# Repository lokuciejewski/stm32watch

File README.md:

# STM32 Watch

## Summary

This project is a simplistic STM32L031K6-based hand watch. It uses two HP's HPDL1414 displays to display up to 6 alphanumeric signs (though only capital letters). For timekeeping I decided to go with DS3231MZ+ and the whole thing is programmed in C using STM32CubeIDE.

## Main functions

New, HCMS-2904 version:

Apart from keeping the time and date, the watch is capable of adjusting its brightness automatically and displaying battery voltage. It uses USB type C for convenient charging (not compatible with chargers that require device ID to be sent) and includes a LED to indicate charging status.

Old, HPDL-1414 version:
Apart from keeping the time and date, the watch is capable of displaying the current ambient temperature and pressure, courtesy of Bosch BMP280 (which can be hot-swapped for BME280 for additional humidity data) and battery voltage. The watch is also equipped with two user-programmable LEDs - green and red by default, one charging indicator LED - yellow and a vibration motor (also fully programmable). It uses USB type C for convenient charging, though it is not compatible with some of the USB-C chargers (those that require device ID to be sent).

## PCB design

The design is currently WIP as the first prototype using HPDL-1414 was produced and verified. The new design will include HCMS-2904 as a replacement and will drop some features and gain some new ones, streamlining the design.

## Case design

There is a simple WIP case design for the HPDL-1414 version, more will come once the new HCMS-2904 pcb is finished.

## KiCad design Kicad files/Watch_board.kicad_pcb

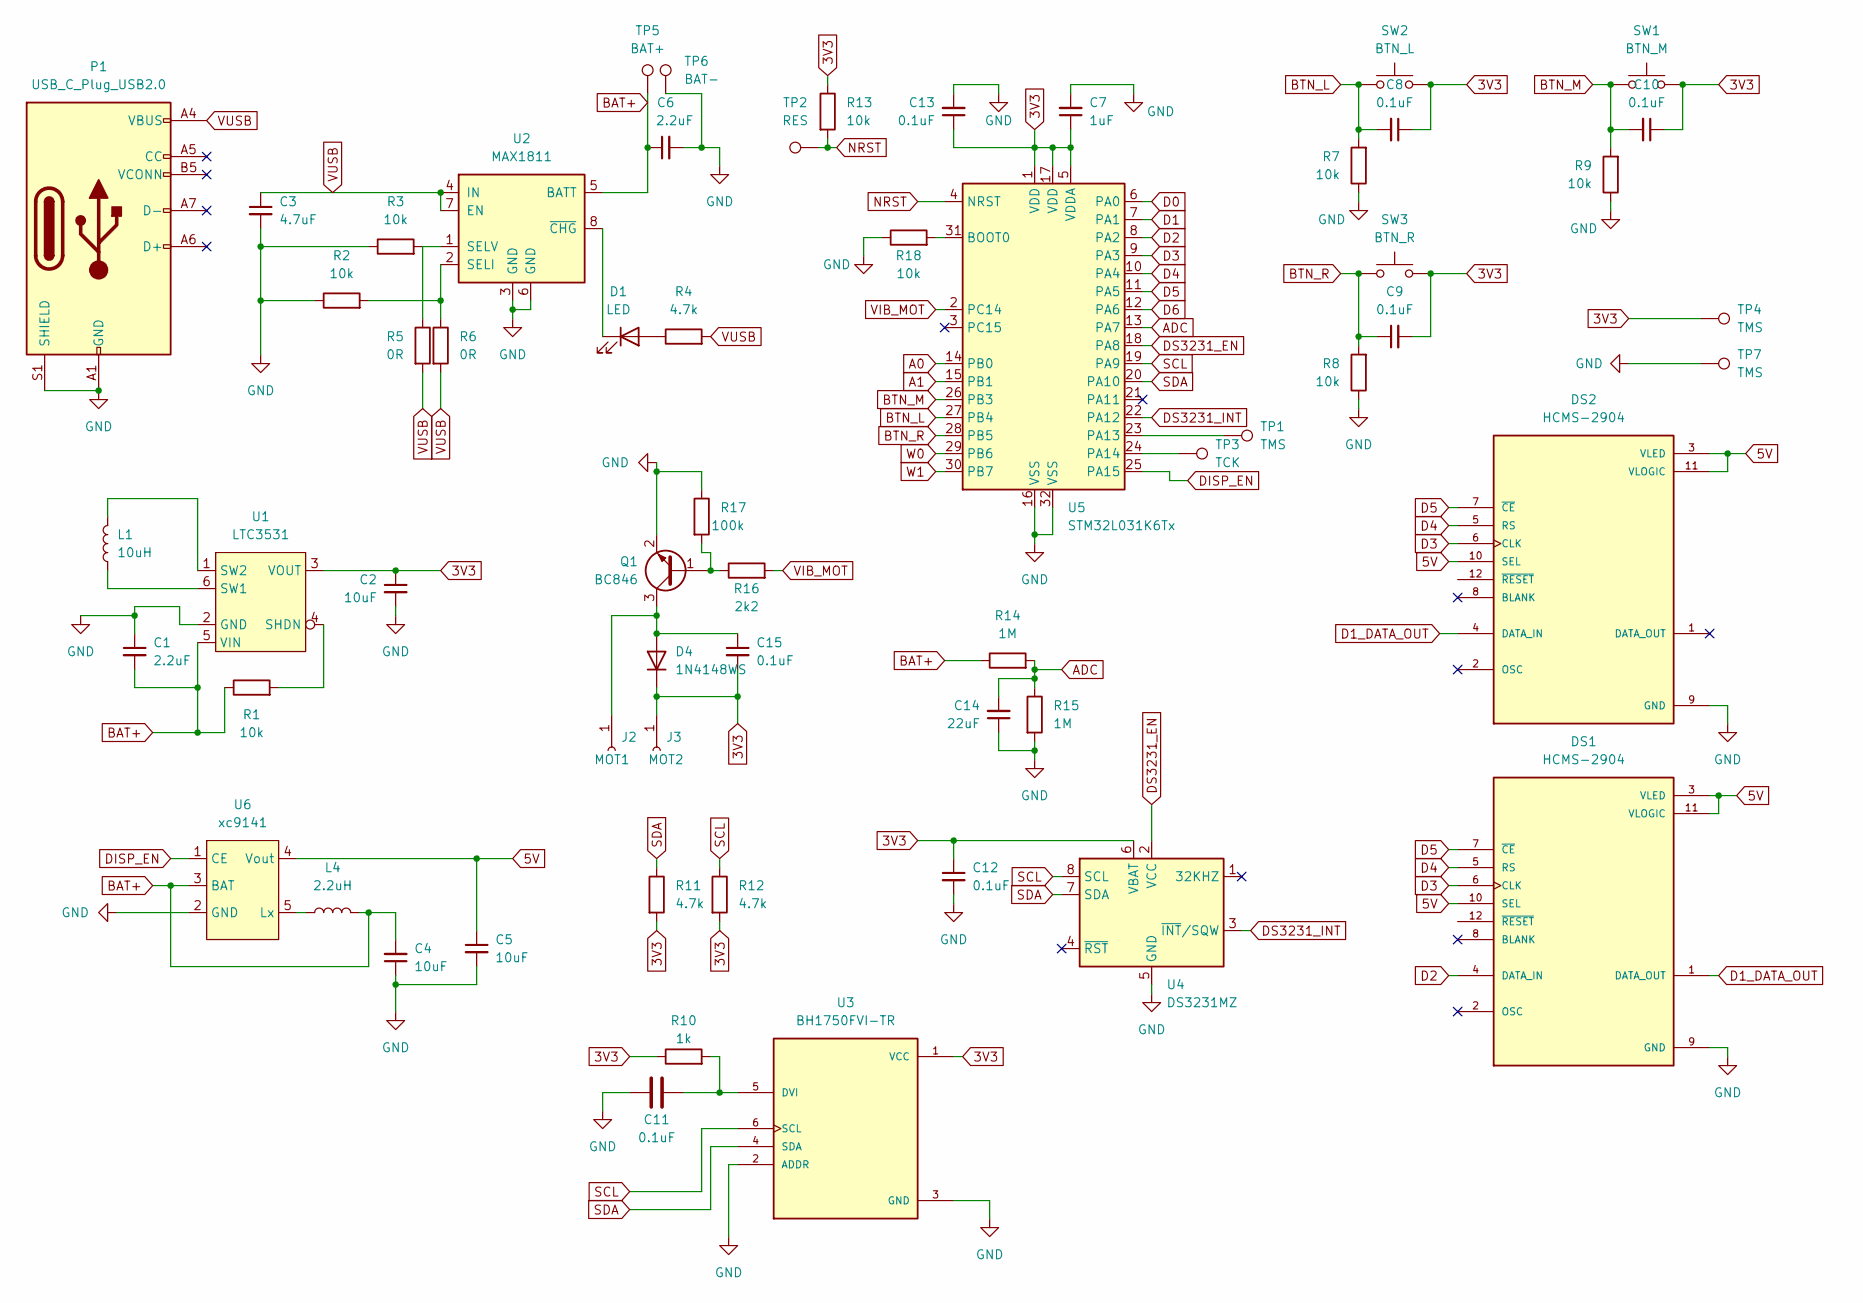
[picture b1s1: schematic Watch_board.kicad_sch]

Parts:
C1, C6: 2.2uF; C_0603_1608Metric_Pad1.08x0.95mm_HandSolder
C2, C4, C5: 10uF; C_0603_1608Metric_Pad1.08x0.95mm_HandSolder
C3: 4.7uF; C_0603_1608Metric_Pad1.08x0.95mm_HandSolder
C7: 1uF; C_0603_1608Metric_Pad1.08x0.95mm_HandSolder
C8, C9, C10, C11, C12, C13, C15: 0.1uF; C_0603_1608Metric_Pad1.08x0.95mm_HandSolder
C14: 22uF; C_0603_1608Metric_Pad1.08x0.95mm_HandSolder
D1: LED; LED_1206_3216Metric_Pad1.42x1.75mm_HandSolder
D4: 1N4148WS; D_SOD-323
DS1, DS2: HCMS-2904; DIPS762W51P254L1778H508Q12; PARTREV N/A
J2: MOT1; TestPoint_Pad_D2.0mm
J3: MOT2; TestPoint_Pad_D2.0mm
L1: 10uH; L_0603_1608Metric_Pad1.05x0.95mm_HandSolder
L4: 2.2uH; L_0603_1608Metric_Pad1.05x0.95mm_HandSolder
P1: USB_C_Plug_USB2.0; TYPE-C-31-M-17_handsolder
Q1: BC846; SOT-23
R1, R2, R3, R7, R8, R9, R13, R18: 10k; R_0603_1608Metric_Pad0.98x0.95mm_HandSolder
R4, R11, R12: 4.7k; R_0603_1608Metric_Pad0.98x0.95mm_HandSolder
R5, R6: 0R; R_0603_1608Metric_Pad0.98x0.95mm_HandSolder
R10: 1k; R_0603_1608Metric_Pad0.98x0.95mm_HandSolder
R14, R15: 1M; R_0603_1608Metric_Pad0.98x0.95mm_HandSolder
R16: 2k2; R_0603_1608Metric_Pad0.98x0.95mm_HandSolder
R17: 100k; R_0603_1608Metric_Pad0.98x0.95mm_HandSolder
SW1: BTN_M; SW_SPST_PTS810
SW2: BTN_L; SW_SPST_PTS810
SW3: BTN_R; SW_SPST_PTS810
TP1, TP4, TP7: TMS; TestPoint_Pad_1.5x1.5mm
TP2: RES; TestPoint_Pad_1.5x1.5mm
TP3: TCK; TestPoint_Pad_1.5x1.5mm
TP5: BAT+; TestPoint_Pad_1.5x1.5mm
TP6: BAT-; TestPoint_Pad_1.5x1.5mm
U1: LTC3531; TSOT-23-6
U2: MAX1811; SOIC-8_3.9x4.9mm_P1.27mm
U3: BH1750FVI-TR; XDCR_BH1750FVI-TR; PARTREV D
U4: DS3231MZ; SOIC-8_3.9x4.9mm_P1.27mm
U5: STM32L031K6Tx; LQFP-32_7x7mm_P0.8mm
U6: xc9141; SOT-23-5

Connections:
3V3: C2.1, C7.1, C8.1, C9.2, C10.1, C12.1, C13.1, C15.2, D4.1 (K), J3.1, R10.1, R11.2, R12.2, R13.1, SW1.2, SW2.2, SW3.2, TP4.1, U1.3 (VOUT), U3.1 (VCC), U4.6 (VBAT), U5.1 (VDD), U5.5 (VDDA), U5.17 (VDD)
5V: C5.1, DS1.3 (VLED), DS1.10 (SEL), DS1.11 (VLOGIC), DS2.3 (VLED), DS2.10 (SEL), DS2.11 (VLOGIC), U6.4 (Vout)
A0: U5.14 (PB0)
A1: U5.15 (PB1)
ADC: C14.2, R14.2, R15.1, U5.13 (PA7)
BAT+: C1.2, C4.2, C6.1, L4.2, R1.1, R14.1, TP5.1, U1.5 (VIN), U2.5 (BATT), U6.3 (BAT)
BTN_L: C8.2, R7.2, SW2.1, U5.27 (PB4)
BTN_M: C10.2, R9.2, SW1.1, U5.26 (PB3)
BTN_R: C9.1, R8.2, SW3.1, U5.28 (PB5)
D0: U5.6 (PA0)
D1: U5.7 (PA1)
D1_DATA_OUT: DS1.1 (DATA_OUT), DS2.4 (DATA_IN)
D2: DS1.4 (DATA_IN), U5.8 (PA2)
D3: DS1.6 (CLK), DS2.6 (CLK), U5.9 (PA3)
D4: DS1.5 (RS), DS2.5 (RS), U5.10 (PA4)
D5: DS1.7 (~CE), DS2.7 (~CE), U5.11 (PA5)
D6: U5.12 (PA6)
DISP_EN: U5.25 (PA15), U6.1 (CE)
DS3231_EN: U4.2 (VCC), U5.18 (PA8)
DS3231_INT: U4.3 (~INT/SQW), U5.22 (PA12)
GND: C1.1, C2.2, C3.2, C4.1, C5.2, C6.2, C7.2, C11.1, C12.2, C13.2, C14.1, DS1.9 (GND), DS2.9 (GND), P1.A1 (GND), P1.A12 (GND), P1.B1 (GND), P1.B12 (GND), P1.S1 (SHIELD), Q1.2 (E), R2.1, R3.1, R7.1, R8.1, R9.1, R15.2, R17.1, R18.1, TP6.1, TP7.1, U1.2 (GND), U2.3 (GND), U2.6 (GND), U3.2 (ADDR), U3.3 (GND), U4.5 (GND), U5.16 (VSS), U5.32 (VSS), U6.2 (GND)
NRST: R13.2, TP2.1, U5.4 (NRST)
unnamed: D1.2 (A), R4.1
unnamed: D1.1 (K), U2.8 (~CHG)
unnamed: C15.1, D4.2 (A), J2.1, Q1.3 (C)
unnamed: Q1.1 (B), R16.1, R17.2
unnamed: R1.2, U1.4 (SHDN)
unnamed: L1.1, U1.6 (SW1)
unnamed: L1.2, U1.1 (SW2)
unnamed: R2.2, R6.1, U2.2 (SELI)
unnamed: R3.2, R5.1, U2.1 (SELV)
unnamed: C11.2, R10.2, U3.5 (DVI)
unnamed: R18.2, U5.31 (BOOT0)
unnamed: TP1.1, U5.23 (PA13)
unnamed: TP3.1, U5.24 (PA14)
unnamed: L4.1, U6.5 (Lx)
SCL: R12.1, U3.6 (SCL), U4.8 (SCL), U5.19 (PA9)
SDA: R11.1, U3.4 (SDA), U4.7 (SDA), U5.20 (PA10)
VIB_MOT: R16.2, U5.2 (PC14)
VUSB: C3.1, P1.A4 (VBUS), P1.A9 (VBUS), P1.B4 (VBUS), P1.B9 (VBUS), R4.2, R5.2, R6.2, U2.4 (IN), U2.7 (EN)
W0: U5.29 (PB6)
W1: U5.30 (PB7)

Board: 2 copper layers, 58 parts (0 on the bottom side), 35 nets, no tracks yet.

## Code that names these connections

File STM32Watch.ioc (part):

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Mcu.Name=STM32L031K(4-6)Tx
Mcu.Package=LQFP32
Mcu.UserName=STM32L031K6Tx
PA0-CK_IN.GPIOParameters=GPIO_PuPd,GPIO_Label
PA0-CK_IN.GPIO_Label=D0
PA0-CK_IN.GPIO_PuPd=GPIO_NOPULL
PA0-CK_IN.Signal=GPIO_Output
PA1.GPIOParameters=GPIO_PuPd,GPIO_Label
PA1.GPIO_Label=D1
PA1.GPIO_PuPd=GPIO_NOPULL
PA1.Signal=GPIO_Output
PA10.Mode=I2C
PA10.Signal=I2C1_SDA
PA11.GPIOParameters=GPIO_Label
PA11.GPIO_Label=LED_R
PA11.Signal=GPIO_Output
PA12.GPIOParameters=GPIO_Label
PA12.GPIO_Label=DS3231_INT
PA12.Signal=GPXTI12
PA13.GPIOParameters=GPIO_Label
PA13.GPIO_Label=TMS
PA13.Mode=Serial_Wire
PA13.Signal=SYS_SWDIO
PA14.GPIOParameters=GPIO_Label
PA14.GPIO_Label=TCK
PA14.Mode=Serial_Wire
PA14.Signal=SYS_SWCLK
PA15.GPIOParameters=GPIO_Label
PA15.GPIO_Label=DISP_EN
PA15.Signal=GPIO_Output
PA2.GPIOParameters=GPIO_PuPd,GPIO_Label
PA2.GPIO_Label=D2
PA2.GPIO_PuPd=GPIO_NOPULL
PA2.Signal=GPIO_Output
PA3.GPIOParameters=GPIO_PuPd,GPIO_Label
PA3.GPIO_Label=D3
PA3.GPIO_PuPd=GPIO_NOPULL
PA3.Signal=GPIO_Output
PA4.GPIOParameters=GPIO_PuPd,GPIO_Label
PA4.GPIO_Label=D4
PA4.GPIO_PuPd=GPIO_NOPULL
PA4.Signal=GPIO_Output
PA5.GPIOParameters=GPIO_PuPd,GPIO_Label
PA5.GPIO_Label=D5
PA5.GPIO_PuPd=GPIO_NOPULL
PA5.Signal=GPIO_Output
PA6.GPIOParameters=GPIO_PuPd,GPIO_Label
PA6.GPIO_Label=D6
PA6.GPIO_PuPd=GPIO_NOPULL
PA6.Signal=GPIO_Output
PA7.GPIOParameters=GPIO_Label
PA7.GPIO_Label=V_BAT_IN
PA7.Mode=IN7
PA7.Signal=ADC_IN7
PA8.GPIOParameters=GPIO_PuPd,GPIO_Label
PA8.GPIO_Label=DS3231_EN
PA8.GPIO_PuPd=GPIO_NOPULL
PA8.Signal=GPIO_Output
PA9.Mode=I2C
PA9.Signal=I2C1_SCL
PB0.GPIOParameters=GPIO_Label
PB0.GPIO_Label=A0
PB0.Signal=GPIO_Output
PB1.GPIOParameters=GPIO_Label
PB1.GPIO_Label=A1
PB1.Signal=GPIO_Output
PB3.GPIOParameters=GPIO_Label
PB3.GPIO_Label=LED_G
PB3.Signal=GPIO_Output
PB4.GPIOParameters=GPIO_Label,GPIO_ModeDefaultEXTI
PB4.GPIO_Label=BTN_L
PB4.GPIO_ModeDefaultEXTI=GPIO_MODE_IT_RISING_FALLING
PB4.Signal=GPXTI4
PB5.GPIOParameters=GPIO_Label,GPIO_ModeDefaultEXTI
PB5.GPIO_Label=BTN_R
PB5.GPIO_ModeDefaultEXTI=GPIO_MODE_IT_RISING_FALLING
PB5.Signal=GPXTI5
PB6.GPIOParameters=GPIO_PuPd,GPIO_Label
PB6.GPIO_Label=W0
PB6.GPIO_PuPd=GPIO_PULLUP
PB6.Signal=GPIO_Output
PB7.GPIOParameters=GPIO_PuPd,GPIO_Label
PB7.GPIO_Label=W1
PB7.GPIO_PuPd=GPIO_PULLUP
PB7.Signal=GPIO_Output
PC14-OSC32_IN.GPIOParameters=GPIO_Label
PC14-OSC32_IN.GPIO_Label=VIB_MOT
PC14-OSC32_IN.Signal=GPIO_Output
RCC.HSE_VALUE=8000000
RCC.SYSCLKFreq_VALUE=32000000
RCC.SYSCLKSource=RCC_SYSCLKSOURCE_PLLCLK
board=NUCLEO-L031K6
boardIOC=true

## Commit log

2022-08-22 added KiCad files
2022-08-22 added STM32CubeIDE files
2022-08-22 added .gitignore, initial README.md
2022-08-22 updated PCB version
2022-08-22 added STL files
2022-08-22 added version
2022-08-22 removed Debug and Release folders
2022-08-24 added date support, more minor changes
2023-12-05 updated to HCMS-2904 (WIP)
2024-01-17 updated kicad schematics to add light sensor, updated code
2024-01-18 added code for bh1750 light sensor
